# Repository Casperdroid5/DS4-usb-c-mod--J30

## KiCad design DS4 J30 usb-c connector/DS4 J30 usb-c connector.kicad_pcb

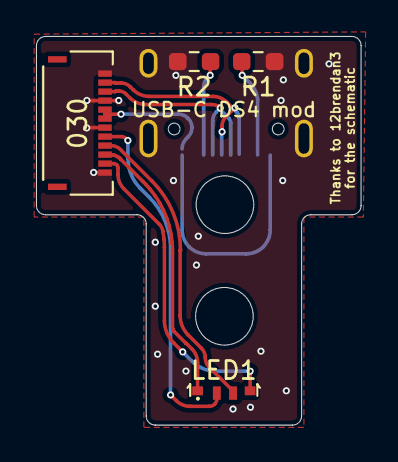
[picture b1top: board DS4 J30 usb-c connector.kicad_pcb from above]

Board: 2 copper layers, 18.0 x 21.6 mm, 5 parts (1 on the bottom side), 10 nets.

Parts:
J1: 030; 503480-1200
LED1: LED_RAGB; FM-3510RGBA-SG
R1, R2: 5.1k; R_0603_1608Metric_Pad0.98x0.95mm_HandSolder
USB1: USB_C_Receptacle_USB2.0; USB_C_Receptacle_HRO_TYPE-C-31-M-12

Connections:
+5V: J1.5, J1.6, USB1.A4, USB1.A9, USB1.B4, USB1.B9
/Annode: J1.8, LED1.2
/B: J1.11, LED1.4
/D+: J1.2, USB1.A6, USB1.B6
/D-: J1.3, USB1.A7, USB1.B7
/G: J1.9, LED1.3
/R: J1.10, LED1.1
GND: J1.1, J1.4, J1.7, J1.12, R1.2, R2.1, USB1.A1, USB1.A12, USB1.B1, USB1.B12, USB1.S1
unnamed: R1.1, USB1.B5
unnamed: R2.2, USB1.A5

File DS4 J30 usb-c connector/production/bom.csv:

Designator,Footprint,Quantity,Value,LCSC Part #
,,1,,
J1,503480-1200,1,030,
LED1,FM-3510RGBA-SG,1,LED_RAGB,
"R1, R2",R_0603_1608Metric_Pad0.98x0.95mm_HandSolder,2,5.1k,
USB1,USB_C_Receptacle_HRO_TYPE-C-31-M-12,1,USB_C_Receptacle_USB2.0,

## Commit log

2022-09-17 First Release
2022-09-17 Cleanup
2022-10-09 enh. silkscreen

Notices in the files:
parts and their libraries:
Copyright 2021 Accelerated Designs. All rights reserved.
